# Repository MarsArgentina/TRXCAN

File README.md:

# TRXCAN
This project aims to develop an open platform that allows CANSAT developers to easily add RF communications and APRS tracking. It will also add GPIO and flight computer control a weather balloon.

This project is intended to fit inside an standardized CANSAT, measuring 66mm in diameter and 3CM in height. 

This project is currently in development. 

Currently the intended platform can be viewed in the following images:

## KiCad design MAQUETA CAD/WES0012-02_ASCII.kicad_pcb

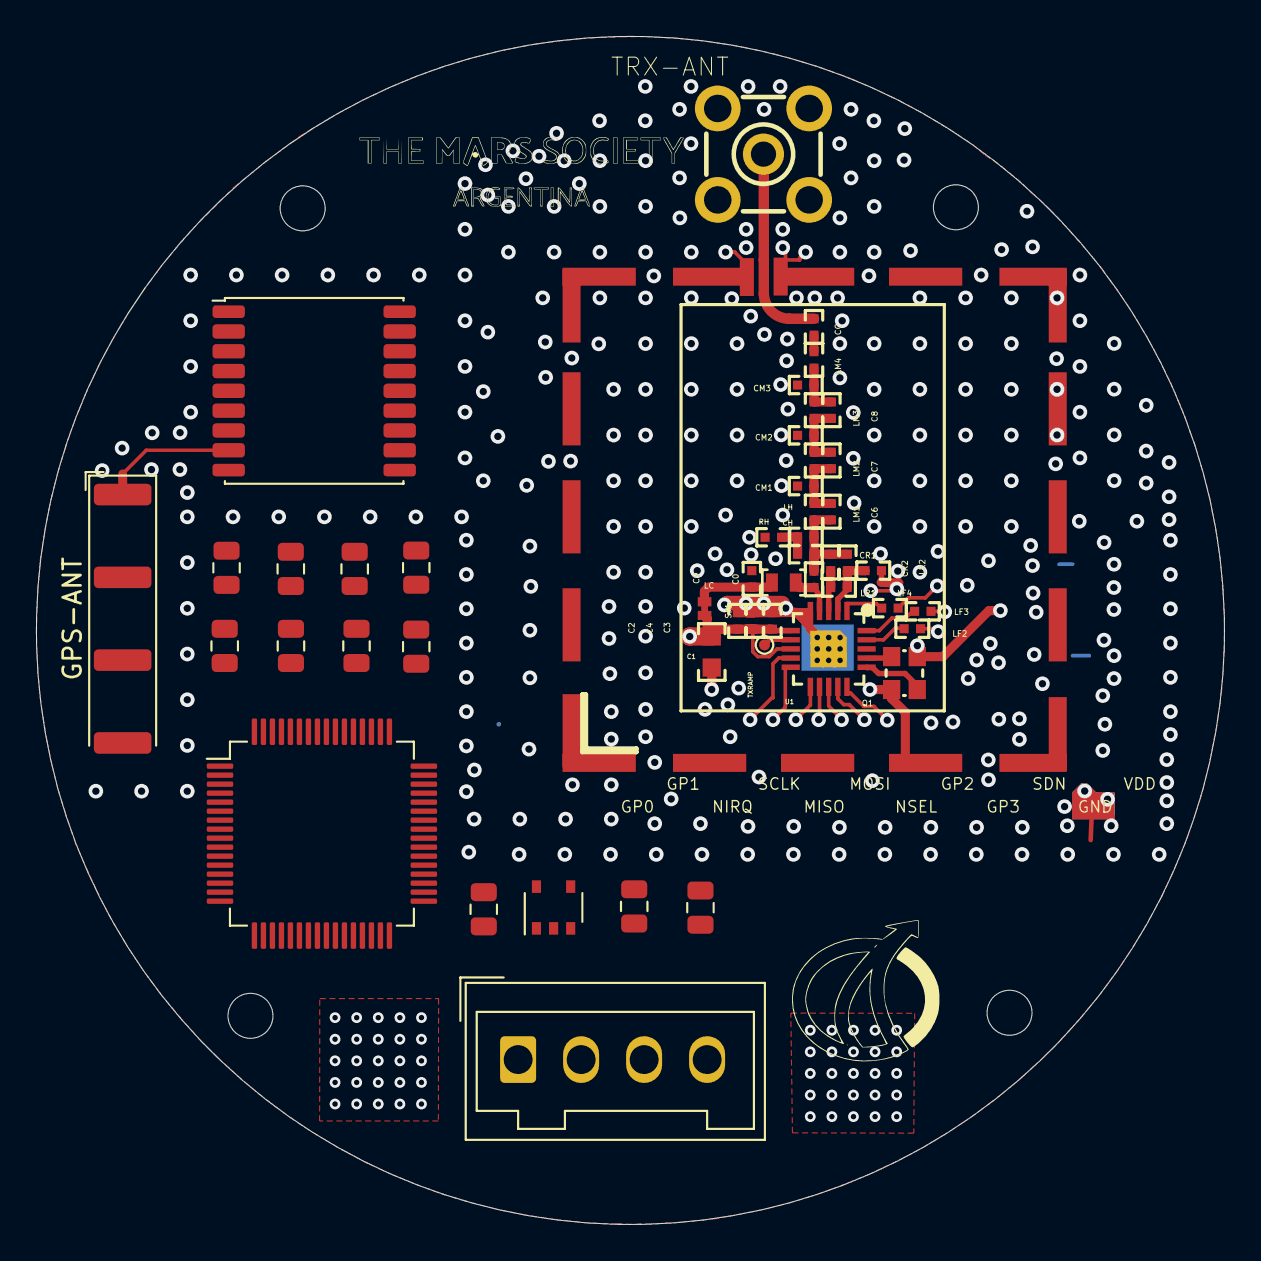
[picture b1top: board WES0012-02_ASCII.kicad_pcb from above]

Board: 4 copper layers, 66.0 x 66.0 mm, 35 parts (0 on the bottom side), 19 nets.

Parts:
C0, C2, C3, C4, C6, C7, C8, C9: SMD0402
C1: SMD0603
CC: SMD0402
CH: SMD0402
CM1, CM2, CM3: SMD0402
CR1, CR2: SMD0402
GPS-ANT: Antenova_SR4G013_GPS
LC: IND0603
LF2, LF3, LF4: SMD0402
LH: SMD0402
LM1, LM2, LM3, LM4: SMD0402
LR1, LR2: SMD0402
Q1: CRYSTAL_4PIN_SMD_2.5X2MM
RH: SMD0402
SJ1: JP_SMD_2P_20X30_SHORT
TRX-ANT: SMA-V
TXRAMP: TESTPOINT_24
U1: QFN-20
U4: SHIELD_BMI-S-203-F

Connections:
$$$6546: TXRAMP.1, U1.7
$$$7296: CC.2, TRX-ANT.1
$$$10983: CH.1, LH.1, RH.2
$$$11456: Q1.3, U1.16
$$$11466: Q1.1, U1.17
$$$30978: LF4.1, U1.1
$$$30982: LF3.1, U1.20
$$$30984: LF2.1, U1.19
GND: C1.1, C2.1, C3.1, C4.1, C9.1, CM1.1, CM2.1, CM3.1, CR1.1, Q1.2, Q1.4, RH.1, TRX-ANT.2, TRX-ANT.3, TRX-ANT.4, TRX-ANT.5, U1.5, U1.EP, U1.EP2, U1.EP3, U1.EP4, U1.EP5, U1.EP6, U1.EP7, U1.EP8, U1.EP9, U4.GND0, U4.GND1, U4.GND2, U4.GND3, U4.GND4, U4.GND5, U4.GND6, U4.GND7, U4.GND8, U4.GND9, U4.GND10, U4.GND11, U4.GND12, U4.GND13, U4.GND14, U4.GND15, U4.GND16, U4.GND17, U4.GND18, U4.GND19
RFVDD: C1.2, C2.2, C3.2, C4.2, SJ1.2, U1.6, U1.8
RFVDD_TX: C9.2, LC.2, SJ1.1
RXN: CR2.2, LR1.1, U1.3
RXP: CR1.2, LR1.2, LR2.2, U1.2
TRX2: C8.1, CM3.2, LM3.1, LM4.2
TX1: C0.2, LC.1, U1.4
TX3: C0.1, C6.2, CH.2, CR2.1, LH.2, LM1.2, LR2.1
TX4: C7.1, C8.2, CM2.2, LM2.1, LM3.2
TX6: C6.1, C7.2, CM1.2, LM1.1, LM2.2
TX7: CC.1, LM4.1
